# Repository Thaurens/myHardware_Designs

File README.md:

<h1 align="center">Welcome to My Hardware Design Hub 🛠️</h1>

<p align="center">
  A centralized repository showcasing my open-source hardware designs, electronic engineering projects, and technical documentation.
</p>

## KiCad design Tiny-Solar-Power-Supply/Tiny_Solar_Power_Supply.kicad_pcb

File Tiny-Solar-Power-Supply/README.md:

<p align="center">

# ☀️ Tiny Solar Power Supply (1.2V to 3.3V Auto-Switching)

This repository contains the hardware design files for a Tiny Solar Power Supply. **I have completed the design of this module, developed as part of Peter Dalmaris' hardware design course on Udemy.** The goal of this project is to repurpose standard solar garden light components (a mini solar panel and a 1.2V Ni-MH rechargeable battery) into a reliable power source for small electronics. Unlike standard garden lights that provide an unregulated voltage, this module outputs a clean, regulated 3.3V, making it ideal for powering low-power microcontrollers and IoT sensors.

## 📌 Project Overview
The core of the design is the **AP3015 DC-DC Boost Converter**, which efficiently steps up the 1.2V battery voltage to 3.3V. To conserve energy, the circuit features an autonomous switching mechanism that detects ambient light conditions entirely through hardware.

## ✨ Key Features
* **Input:** 1.2V Ni-MH Rechargeable Battery (AA/AAA) & Mini Solar Panel.
* **Output:** Regulated 3.3V DC.
* **Hardware Auto-Sleep/Wake:**
  * ☀️ **Day Mode (Charging):** The solar panel charges the battery. The panel voltage drives the gate of a 2N7002 MOSFET, pulling the `SHDN` (Shutdown) pin of the AP3015 to ground. The regulator sleeps, and the 3.3V output is disabled.
  * 🌙 **Night Mode (Discharging):** When the panel voltage drops in the dark, the MOSFET turns off. The AP3015 wakes up and begins boosting the battery voltage to 3.3V.

## 🛠️ Working Principle & Topology
The circuit can be divided into three main stages:
1. **Charging Stage:** Energy from the solar panel flows through a Schottky diode (SS14) into the battery, preventing reverse leakage at night.
2. **Switching Stage:** The Q1 MOSFET acts as a light-dependent switch. It toggles the regulator's shutdown pin based on the presence of solar voltage.
3. **Boost Stage:** The U1 IC (AP3015) drives an inductor (L1, 10uH). The resulting flyback voltage is rectified by D1 and smoothed by C2. The feedback voltage divider (R1 and R2) strictly maintains the output at 3.3V.

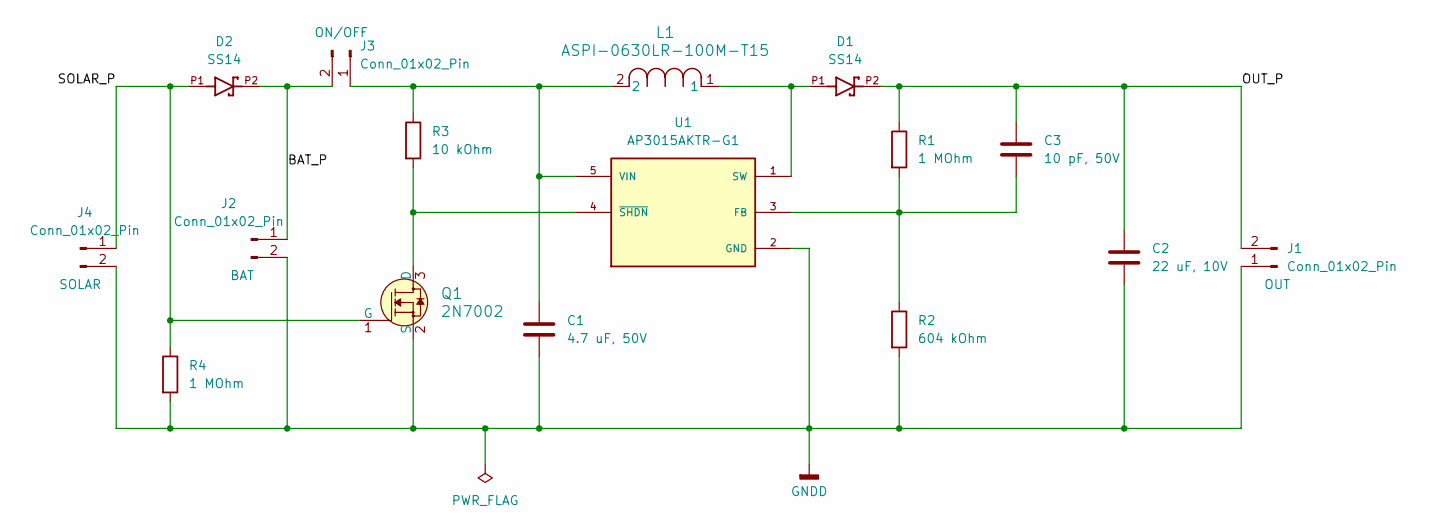
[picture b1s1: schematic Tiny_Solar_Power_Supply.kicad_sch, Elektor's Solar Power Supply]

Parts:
C1: 4.7 uF, 50V; C_0805_2012Metric
C2: 22 uF, 10V; C_1206_3216Metric
C3: 10 pF, 50V; C_0805_2012Metric
D1, D2: SS14; SMA
J1, J2, J3: Conn_01x02_Pin; PinHeader_1x02_P2.54mm_Vertical
J4: Conn_01x02_Pin; PinHeader_1x02_P2.54mm_Horizontal
L1: ASPI-0630LR-100M-T15; IND_ASPI-0630LR_ABR
Q1: 2N7002; SOT-23-3; MPN 2N7002; Digi-Key_PN 2N7002NCT-ND
R1, R4: 1 MOhm; R_0805_2012Metric
R2: 604 kOhm; R_0805_2012Metric
R3: 10 kOhm; R_0805_2012Metric
U1: AP3015AKTR-G1; SOT95P280X145-5N; PARTREV 1.4

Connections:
/BAT_P: D2.P2, J2.1, J3.2
/OUT_P: C2.1, C3.1, D1.P2, J1.2, R1.1
/SOLAR_P: D2.P1, J4.1, Q1.1 (G), R4.1
GNDD: C1.2, C2.2, J1.1, J2.2, J4.2, Q1.2 (S), R2.2, R4.2, U1.2 (GND)
unnamed: C1.1, J3.1, L1.2, R3.1, U1.5 (VIN)
unnamed: Q1.3 (D), R3.2, U1.4 (~SHDN)
unnamed: C3.2, R1.2, R2.1, U1.3 (FB)
unnamed: D1.P1, L1.1, U1.1 (SW)

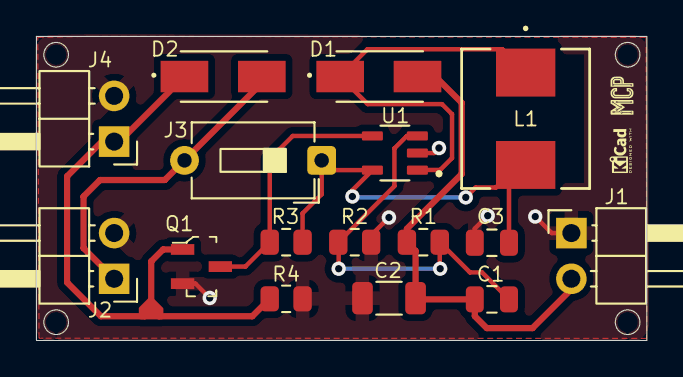
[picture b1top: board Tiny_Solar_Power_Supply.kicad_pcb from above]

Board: 2 copper layers, 33.9 x 16.9 mm, 16 parts (0 on the bottom side), 8 nets.

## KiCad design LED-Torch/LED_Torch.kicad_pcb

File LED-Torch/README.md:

<p align="center">

<h1 align="center">Miniature LED Torch 🔦</h1>

## 🌟 Project Highlights

* **Ultra-Minimalist Design:** The entire circuit utilizes only four easily identifiable, through-hole components, making the BOM and sourcing incredibly manageable.
* **Incredibly Simple Assembly:** No microscopic surface-mount (SMD) parts. Ideal for learning how to solder with immediate visual results.
* **Core Electronic Principles:** Demonstrates the most fundamental hardware loop: a power source, a mechanical switch, a current-limiting resistor, and an LED.
* **Efficient Board Layout:** Intuitive component placement on a highly efficient board, minimizing manufacturing complexity.

## ⚙️ Technical Specifications
<div align="center">

| Component | Details / Value |
| :--- | :--- |
| **Power Source (BT1)** | 3V CR2032 Coin Cell Battery |
| **Light Source (D1)** | Standard 5mm Through-Hole LED |
| **Control (SW1)** | 4-Pin Tactile Push Button |
| **Current Limiter (R1)** | Axial Through-Hole Resistor |

</div>

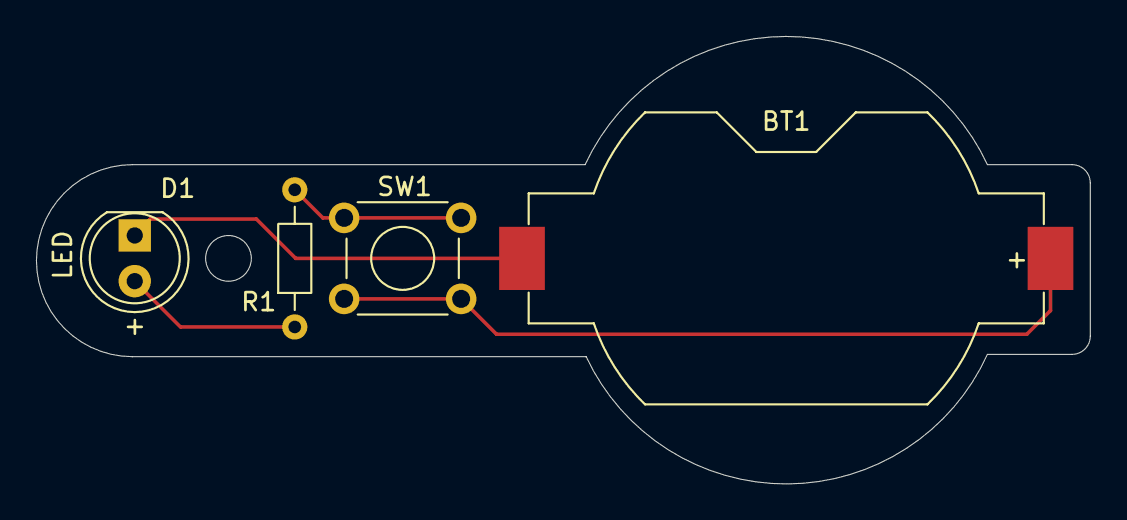
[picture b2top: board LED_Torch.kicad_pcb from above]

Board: 2 copper layers, 58.5 x 24.9 mm, 5 parts (1 on the bottom side), 4 nets.

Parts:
BT1: Battery_Cell; BatteryHolder_Keystone_1058_1x2032
D1: LED; LED_D5.0mm
G1: LOGO
R1: R; R_Axial_DIN0204_L3.6mm_D1.6mm_P7.62mm_Horizontal
SW1: SW_DPST_x2; SW_TH_Tactile_Omron_B3F-100x

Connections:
/Bat_pos: BT1.1 (+), SW1.2 (B)
/LED_Anode: D1.2 (A), R1.1
/LED_Cathode: BT1.2 (-), D1.1 (K)
unnamed: R1.2, SW1.1 (A)

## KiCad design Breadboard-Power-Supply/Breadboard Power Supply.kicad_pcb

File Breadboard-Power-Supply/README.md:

<p align="center">

<h1 align="center">Breadboard Power Supply Module ⚡</h1>

## 🛠️ Technical Highlights

* 🔌 **Master Power Control**
    Utilizes a barrel jack connector for the primary DC input (e.g., +12V). It features an integrated master slide switch for direct, hardware-level on/off control of the entire circuit.
* ⚡ **Dual Voltage Regulation**
    Employs an LM7805 linear regulator for the +5V rail and an LM317 adjustable regulator (configured via a resistor divider) for the +3.3V rail. Both rails are stabilized with bypass capacitors.
* 🔀 **Independent Output Routing**
    Dual 3-pin jumper headers allow the user to independently route either +5V or +3.3V to the top and bottom breadboard rails without requiring structural modifications.
* 🔗 **Auxiliary Terminals**
    Includes onboard screw terminals to securely power external sensors or peripheral modules directly from the main PCB.

> **System Benefit:** This module eliminates the need for multiple external power supplies, ensuring precise and safe voltage management for mixed-signal embedded systems.

## ⚙️ Technical Specifications

<div align="center">

| Feature / Component | Details / Specifications |
| :--- | :--- |
| **Primary Input** | DC Barrel Jack (Optimal: +7V to +12V) |
| **+5V Regulation** | LM7805 Linear Voltage Regulator |
| **+3.3V Regulation** | LM317 Adjustable Regulator (Divider Configured) |
| **Breadboard Routing** | Dual 3-Pin Headers (J3, J4) |
| **Auxiliary Output** | Onboard Screw Terminals (J5, J7) |
| **Status Indicator** | Power-ON Red LED (D1) |

</div>

---
*Note: This project was developed based on the hardware design principles taught in Dr. Peter Dalmaris's Udemy course.*

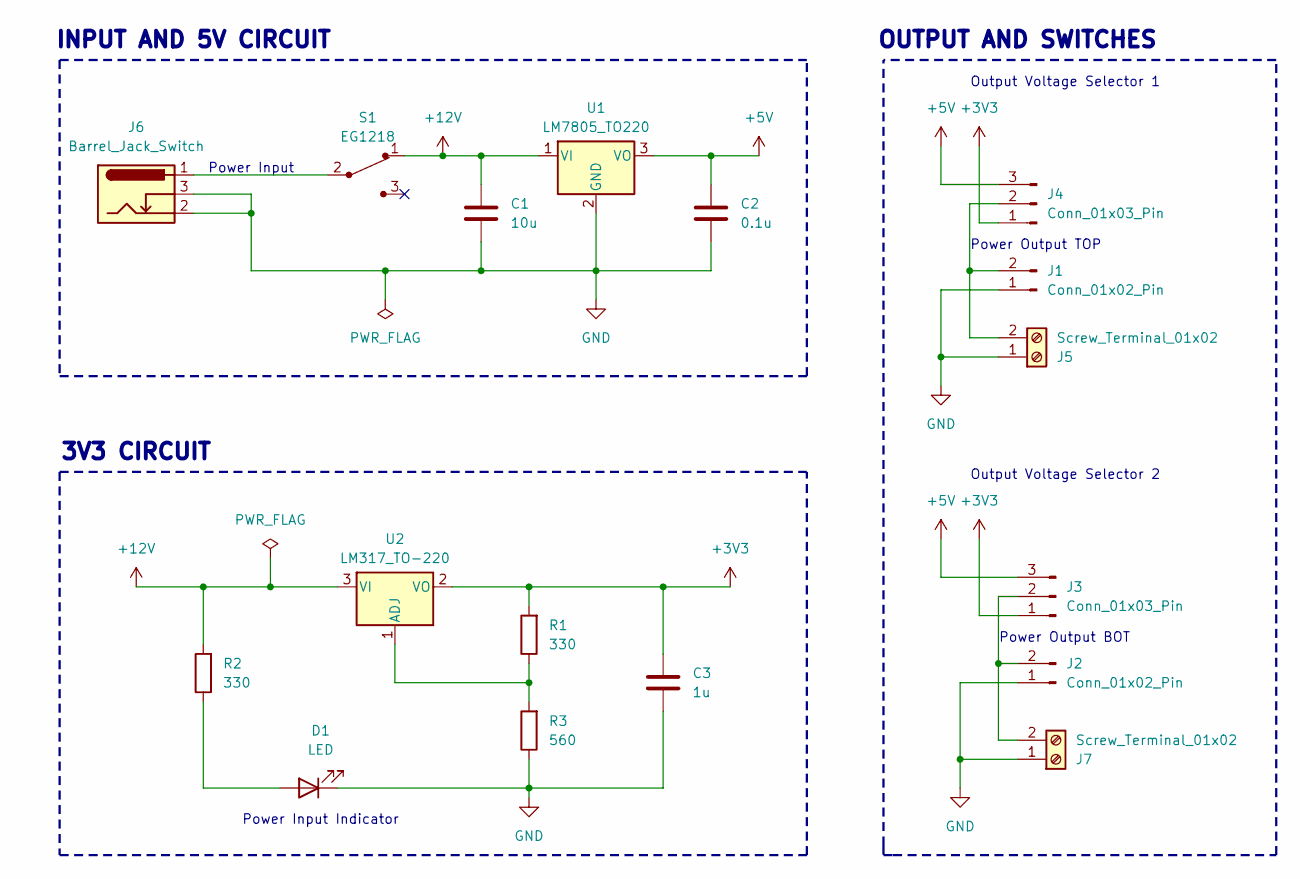
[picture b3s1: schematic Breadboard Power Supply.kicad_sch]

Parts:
C1: 10u; C_Disc_D3.0mm_W1.6mm_P2.50mm
C2: 0.1u; C_Disc_D3.0mm_W1.6mm_P2.50mm
C3: 1u; C_Disc_D3.0mm_W1.6mm_P2.50mm
D1: LED; LED_D5.0mm
J1, J2: Conn_01x02_Pin; PinHeader_1x02_P2.54mm_Vertical
J3, J4: Conn_01x03_Pin; PinHeader_1x03_P2.54mm_Vertical
J5, J7: Screw_Terminal_01x02; TerminalBlock_bornier-2_P5.08mm
J6: Barrel_Jack_Switch; BarrelJack_Horizontal
R1, R2: 330; R_Axial_DIN0204_L3.6mm_D1.6mm_P7.62mm_Horizontal
R3: 560; R_Axial_DIN0204_L3.6mm_D1.6mm_P7.62mm_Horizontal
S1: EG1218; Switch_Slide_11.6x4mm_EG1218; MPN EG1218; Digi-Key_PN EG1903-ND
U1: LM7805_TO220; TO-220-3_Vertical
U2: LM317_TO-220; TO-220-3_Vertical

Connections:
+3V3: C3.1, J3.1, J4.1, R1.2, U2.2 (VO)
+5V: C2.1, J3.3, J4.3, U1.3 (VO)
+12V: C1.1, R2.2, S1.1, U1.1 (VI), U2.3 (VI)
GND: C1.2, C2.2, C3.2, D1.1 (K), J1.1, J2.1, J5.1, J6.2, J6.3, J7.1, R3.1, U1.2 (GND)
unnamed: D1.2 (A), R2.1
unnamed: J1.2, J4.2, J5.2
unnamed: J2.2, J3.2, J7.2
unnamed: J6.1, S1.2
unnamed: R1.1, R3.2, U2.1 (ADJ)

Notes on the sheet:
Power Output TOP
Output Voltage Selector 1
INPUT AND 5V CIRCUIT
Output Voltage Selector 2
3V3 CIRCUIT
Power Input
Power Output BOT
OUTPUT AND SWITCHES
Power Input Indicator

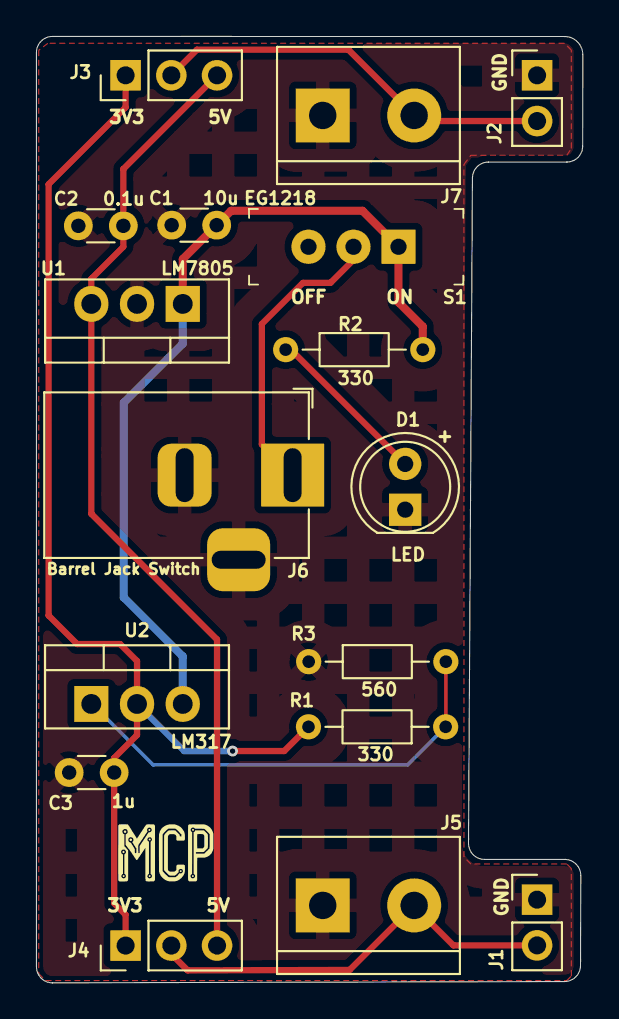
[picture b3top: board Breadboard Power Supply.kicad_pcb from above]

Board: 2 copper layers, 30.4 x 52.6 mm, 17 parts (0 on the bottom side), 9 nets.
